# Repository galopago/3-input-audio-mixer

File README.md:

# MEZCLADOR DE 3 ENTRADAS CON AMPLIFICADOR OPERACIONAL LF353

Mezclador para 3 entradas

## Como usar este repositorio?

El proyecto fue desarrollado en Kicad Version 5.1

## Estructura de carpetas

* El directorio principal o raiz contiene todos los archivos fuentes en Kicad: proyecto, esquematico y circuito impreso

* El directorio gerber contiene los archivos necesarios para la fabricacion de las tarjetas de circuito impreso.

* El directorio ensamble contiene los archivos para ensamble automatizado: Lista de materiales (BOM) y archivo de centroides.

* El directorio info contiene informacion adicional sobre la tarjeta en otros formatos como PDF e imagenes.

* El directorio library contiene simbolos esquematicos adicionales que no vienen en la instalacion por defecto de KiCad

* El directorio modules contiene footprints adicionales que no vienen en la instalacion por defecto de KiCad

## Licencia

Este es un proyecto de Hardware Libre y esta licenciado bajo [Creative Commons Attribution 4.0 International License](http://creativecommons.org/licenses/by/4.0/)

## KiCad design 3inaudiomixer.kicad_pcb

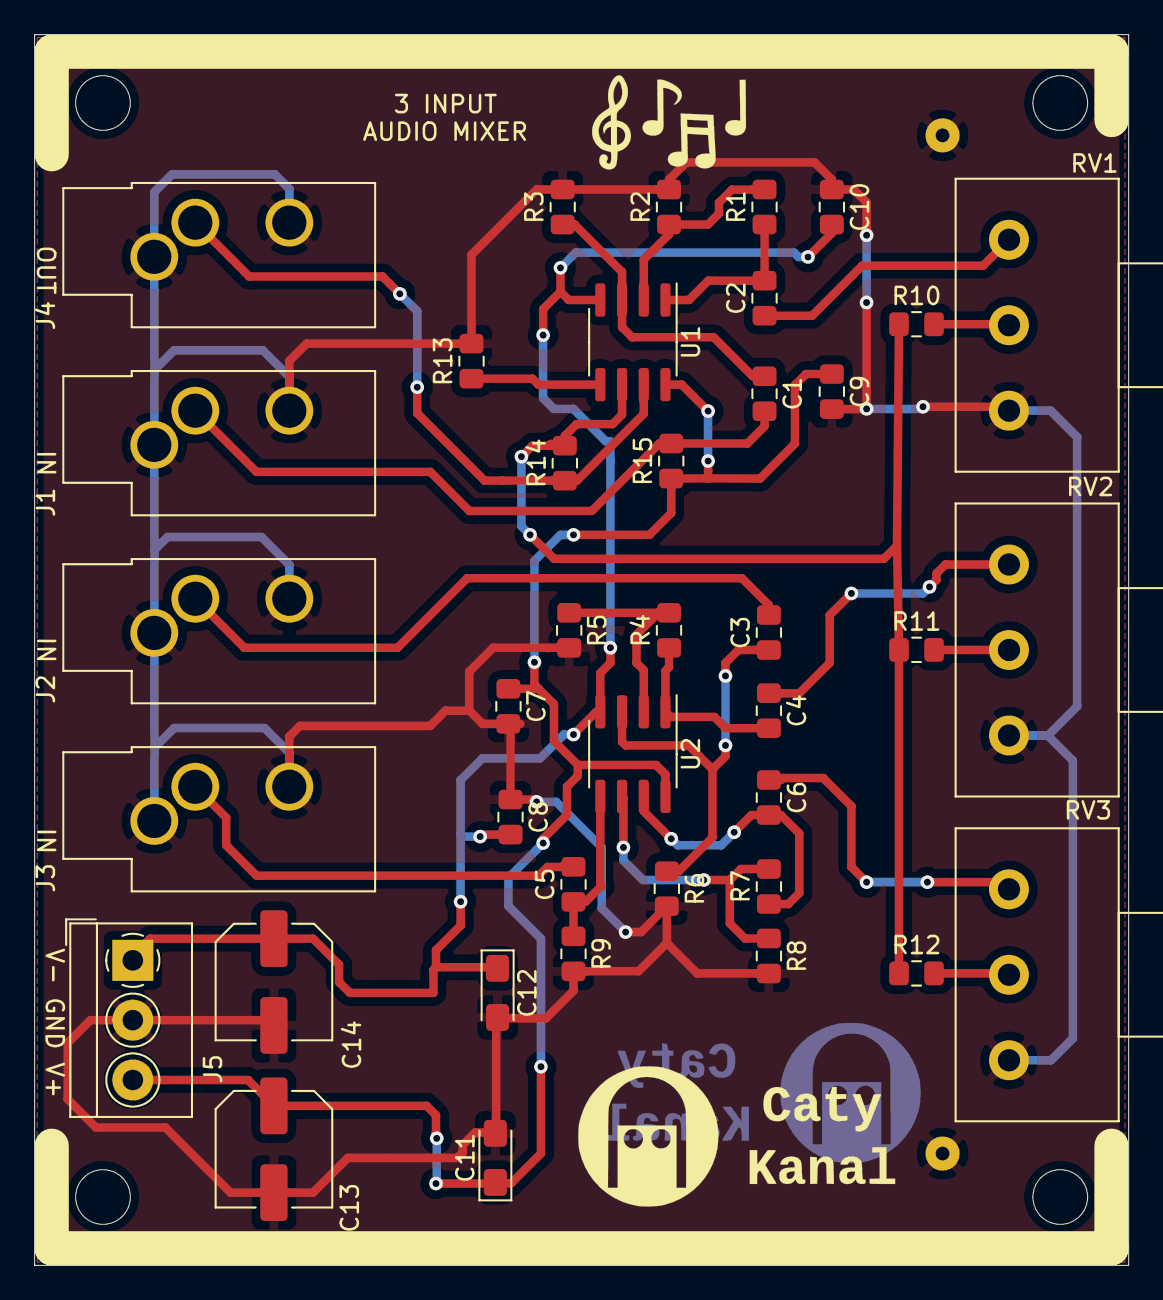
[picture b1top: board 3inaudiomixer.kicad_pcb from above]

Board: 2 copper layers, 64.0 x 72.0 mm, 39 parts (0 on the bottom side), 24 nets.

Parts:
C1, C2, C3, C4, C5, C6: 0.1uF; C_0805_2012Metric_Pad1.15x1.40mm_HandSolder
C7, C8, C9, C10: 100nF; C_0805_2012Metric_Pad1.15x1.40mm_HandSolder
C11, C12: 10uF; CP_EIA-3216-18_Kemet-A_Pad1.58x1.35mm_HandSolder
C13, C14: 220uF; C_Elec_6.3x7.7
J1, J2, J3, J4: AudioJack3; Jack_3.5mm_CUI_SJ1-3533NG_Horizontal_CircularHoles
J5: Conn_01x03_Female; TerminalBlock_4Ucon_1x03_P3.50mm_Horizontal
R1, R4, R7, R10, R11, R12, R14: 100k; R_0805_2012Metric_Pad1.15x1.40mm_HandSolder
R2, R5, R8: 10k; R_0805_2012Metric_Pad1.15x1.40mm_HandSolder
R3, R6, R9: 1.5M; R_0805_2012Metric_Pad1.15x1.40mm_HandSolder
R13: 22k; R_0805_2012Metric_Pad1.15x1.40mm_HandSolder
R15: 20k; R_0805_2012Metric_Pad1.15x1.40mm_HandSolder
RV1, RV2, RV3: 100k; Potentiometer_Omeg_PC16BU_Horizontal
U1, U2: LF353D; SOIC-8_3.9x4.9mm_P1.27mm

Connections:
unnamed: C1.1, R3.1, U1.3
unnamed: C1.2, J1.T, R15.2
unnamed: C2.1, RV1.3
unnamed: C2.2, R1.1, U1.1
unnamed: C3.1, R6.1, U2.3
unnamed: C3.2, J2.T
unnamed: C4.1, RV2.3
unnamed: C4.2, R4.1, U2.1
unnamed: C5.1, R9.1, U2.5
unnamed: C5.2, J3.T
unnamed: C6.1, RV3.3
unnamed: C6.2, R7.1, U2.7
unnamed: C7.2, C8.1, C9.2, C10.1, C11.2, C12.2, C13.2, C14.2, J1.R, J1.S, J2.R, J2.S, J3.R, J3.S, J4.R, J4.S, J5.2, R2.2, R3.2, R5.2, R6.2, R8.2, R9.2, R13.2, RV1.1, RV2.1, RV3.1
unnamed: C8.2, C10.2, C12.1, C14.1, J5.1, U1.4, U2.4
unnamed: C7.1, C9.1, C11.1, C13.1, J5.3, R15.1, U1.8, U2.8
unnamed: J4.T, R14.1, U1.7
unnamed: R1.2, R2.1, U1.2
unnamed: R4.2, R5.1, U2.2
unnamed: R7.2, R8.1, U2.6
unnamed: R10.1, R11.1, R12.1, R14.2, U1.6
unnamed: R10.2, RV1.2
unnamed: R11.2, RV2.2
unnamed: R12.2, RV3.2
unnamed: R13.1, U1.5

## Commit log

2021-05-23 primer commit
2021-05-23 datasheets
2021-05-23 opamp libraries
2021-05-23 some sch components added
2021-05-23 almost all components placed
2021-05-24 some traces routed
2021-05-24 all traces routed, beta board
2021-06-02 mounting holes
2021-06-03 all traces routed & ground planes
2021-06-08 scaled down logo
2021-06-08 pcb finished
2021-06-08 sch components value added
2021-06-08 changed repo pic
2021-06-08 added 3d view pictures
2021-06-09 capacitor footprint fix
2021-06-09 capacitor fix updated pics
2021-06-10 removed voltage regulators
